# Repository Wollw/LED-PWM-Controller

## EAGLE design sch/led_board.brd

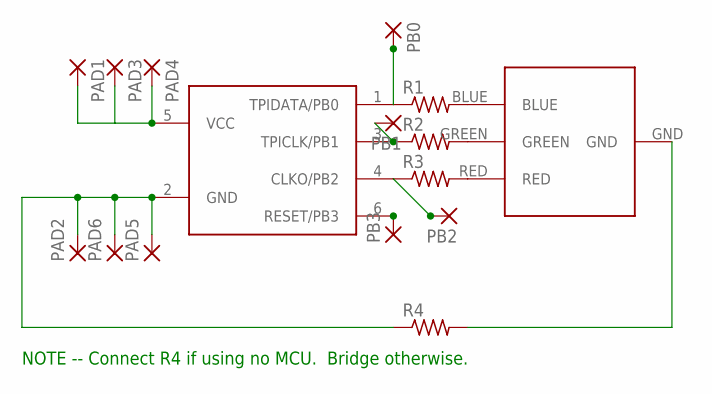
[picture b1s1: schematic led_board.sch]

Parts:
PAD1, PAD2, PAD3, PAD4, PAD5, PAD6: 1,6/0,8
PB0, PB1, PB2, PB3: 1,6/0,8
R1, R2, R3, R4: R-US_M1206; M1206
U$1: BIVAR-RGB-LED; 7.6X7.6MM-LED
U$2: ATTINY10SOT; SOT23-6

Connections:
unnamed: PAD2.1, PAD5.1, PAD6.1, R4.1, U$2.2 (GND)
unnamed: R1.2, U$1.BLUE
unnamed: R2.2, U$1.GREEN
unnamed: R3.2, U$1.RED
unnamed: R4.2, U$1.GND
PB0: PB0.1, R1.1, U$2.1 (TPIDATA/PB0)
PB1: PB1.1, R2.1, U$2.3 (TPICLK/PB1)
PB2: PB2.1, R3.1, U$2.4 (CLKO/PB2)
PB3: PB3.1, U$2.6 (RESET/PB3)
VCC: PAD1.1, PAD3.1, PAD4.1, U$2.5 (VCC)

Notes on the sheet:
NOTE -- Connect R4 if using no MCU. Bridge otherwise.

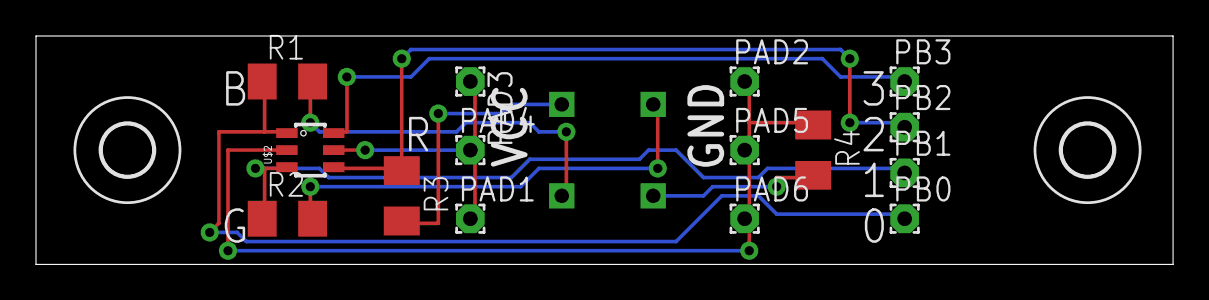
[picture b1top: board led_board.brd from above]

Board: 2 copper layers, 63.2 x 12.7 mm, 18 parts (1 on the bottom side), 10 nets.

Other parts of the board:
E$1, E$2: 2,8

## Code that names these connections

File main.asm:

;;  vim: expandtab
;;  Multicolor LED Controller
;;
;;  This is firmware for an attiny4/5/9/10 for causing a multicolor LED
;;  to change between two colors.  PB0 is connected to one pin of the LED
;;  and PB1 to the other.  PB0 is used as a PWM output which is controlled
;;  by the state of PB2.  When PB2 goes low the LED's color attached to
;;  PB0 fades out.  When PB2 goes high again the color fades back in.
.NOLIST
.INCLUDE "defs.inc"
.LIST

.EQU    PWM_MIN	=	0x02
.EQU    PWM_MAX	=	0xf0

.ORG    0x0000
    rjmp    RESET
.ORG    0x0004
    rjmp    TIM0_OVF
.ORG    0x0040

RESET:
    ;; Clock prescaler of 256 to save power (?)
    ldi     TEMP0,      0xD8
    ldi     TEMP1,      0b1000
    out     CCP,        TEMP0
    out     CLKPSR,     TEMP1

    ;; PB2 is our input used to check if we should
    ;; fade the PWM color in or out so we enable the pullup
    ;; we also enable the pullup on PB3 so potentially save power
    ldi     TEMP0,      0b1100
    out     PUEB,       TEMP0

    ;; PB0 and PB1 are outputs for the LED
    ;; PB0 is controlled usign Fast PWM so we only turn PB1 on here
    ldi     TEMP0,      0b0011
    out     DDRB,       TEMP0
    ldi     TEMP0,      0b0010
    out     PORTB,      TEMP0

    ;; 8-bit Fast PWM on OC0A so we can fade 
    ldi     TEMP1,      0b10000001
    ldi     TEMP0,      0b00001001
    out     TCCR0A,     TEMP1
    out     TCCR0B,     TEMP0

    ;; interrupt on timer overflow
    ;; which is when we update the PWM reference
    ldi     TEMP0,      0b001
    out     TIMSK0,     TEMP0

    ;; Start Fast PWM with a low reference
    ;; meaning it starts out close to off
    ldi     TEMP1,      0x00
    ldi     TEMP0,      PWM_MIN
    out     OCR0AH,     TEMP1
    out     OCR0AL,     TEMP0
    ldi     OCRVAL,     0x40

    ;; Disable ADC to save power
    ldi     TEMP0,      0b10
    out     PRR,        TEMP0

    sei
    rjmp    LOOP

;; Loop forever and sleep a lot
LOOP:
    ldi     TEMP0,      0b1
    out     SMCR,       TEMP0
    sleep
    ldi     TEMP0,      0b0
    out     SMCR,       TEMP0
    rjmp    LOOP


;; When timer overflows increment or decrement based on state of PB2.
;; We don't increment if we're at PWM_HIGH and don't decrement if 
;; we're at PWM_LOW.  If PB2 is high we try to increment, otherwise we
;; try to decrement.
TIM0_OVF:
    cli
    ldi     TEMP0,      0x00
    sbic    PINB,       2
    rjmp    INC_OCRVAL
    rjmp    DEC_OCRVAL
TIM0_OVF_EXIT:
    out     OCR0AH,    TEMP0
    out     OCR0AL,    OCRVAL
    sei
    reti

;; Increment the reference if we aren't at PWM_MAX already
INC_OCRVAL:
    cpi     OCRVAL,     PWM_MAX
    brsh    TIM0_OVF_EXIT
    inc     OCRVAL
    rjmp    TIM0_OVF_EXIT

;; Decrement the reference if we aren't at PWM_MIN already
DEC_OCRVAL:
    cpi     OCRVAL,     PWM_MIN
    brlo    TIM0_OVF_EXIT
    dec     OCRVAL
    rjmp    TIM0_OVF_EXIT

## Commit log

2012-02-17 cleaned up a bit
2012-02-17 forgot the defs.inc file before
2012-02-17 updated gitignore file
2012-02-18 just making sure latest version is up
2012-02-18 changed constants
2012-02-18 removed old comment
2012-02-18 added power saving stuff
2012-02-18 enabled pullup on PB3
2012-02-18 moved PWM_MIN and PWM_MAX definitions to main.asm for easy changing
2012-02-18 recompiled hex
2012-02-19 Added license
2012-02-19 changed license
2012-02-19 moved LED board schematics into this repo
2012-02-19 fixed name of sch directory
2012-02-25 added parts list
2012-02-25 changed resistor values to bring the current drawn from the MCU under its max output
2012-02-29 recreated schematic and pcb files in KiCAD
2012-03-07 changed makefile to use avrisp2 since I have that programmer now and it's a LOT better for programming TPI mode than bitbanging over an ftdi chip
2012-04-01 added todo list
2012-04-01 fixed some problems with the pcb and schematic.
2012-04-14 fixed PARTS listing
